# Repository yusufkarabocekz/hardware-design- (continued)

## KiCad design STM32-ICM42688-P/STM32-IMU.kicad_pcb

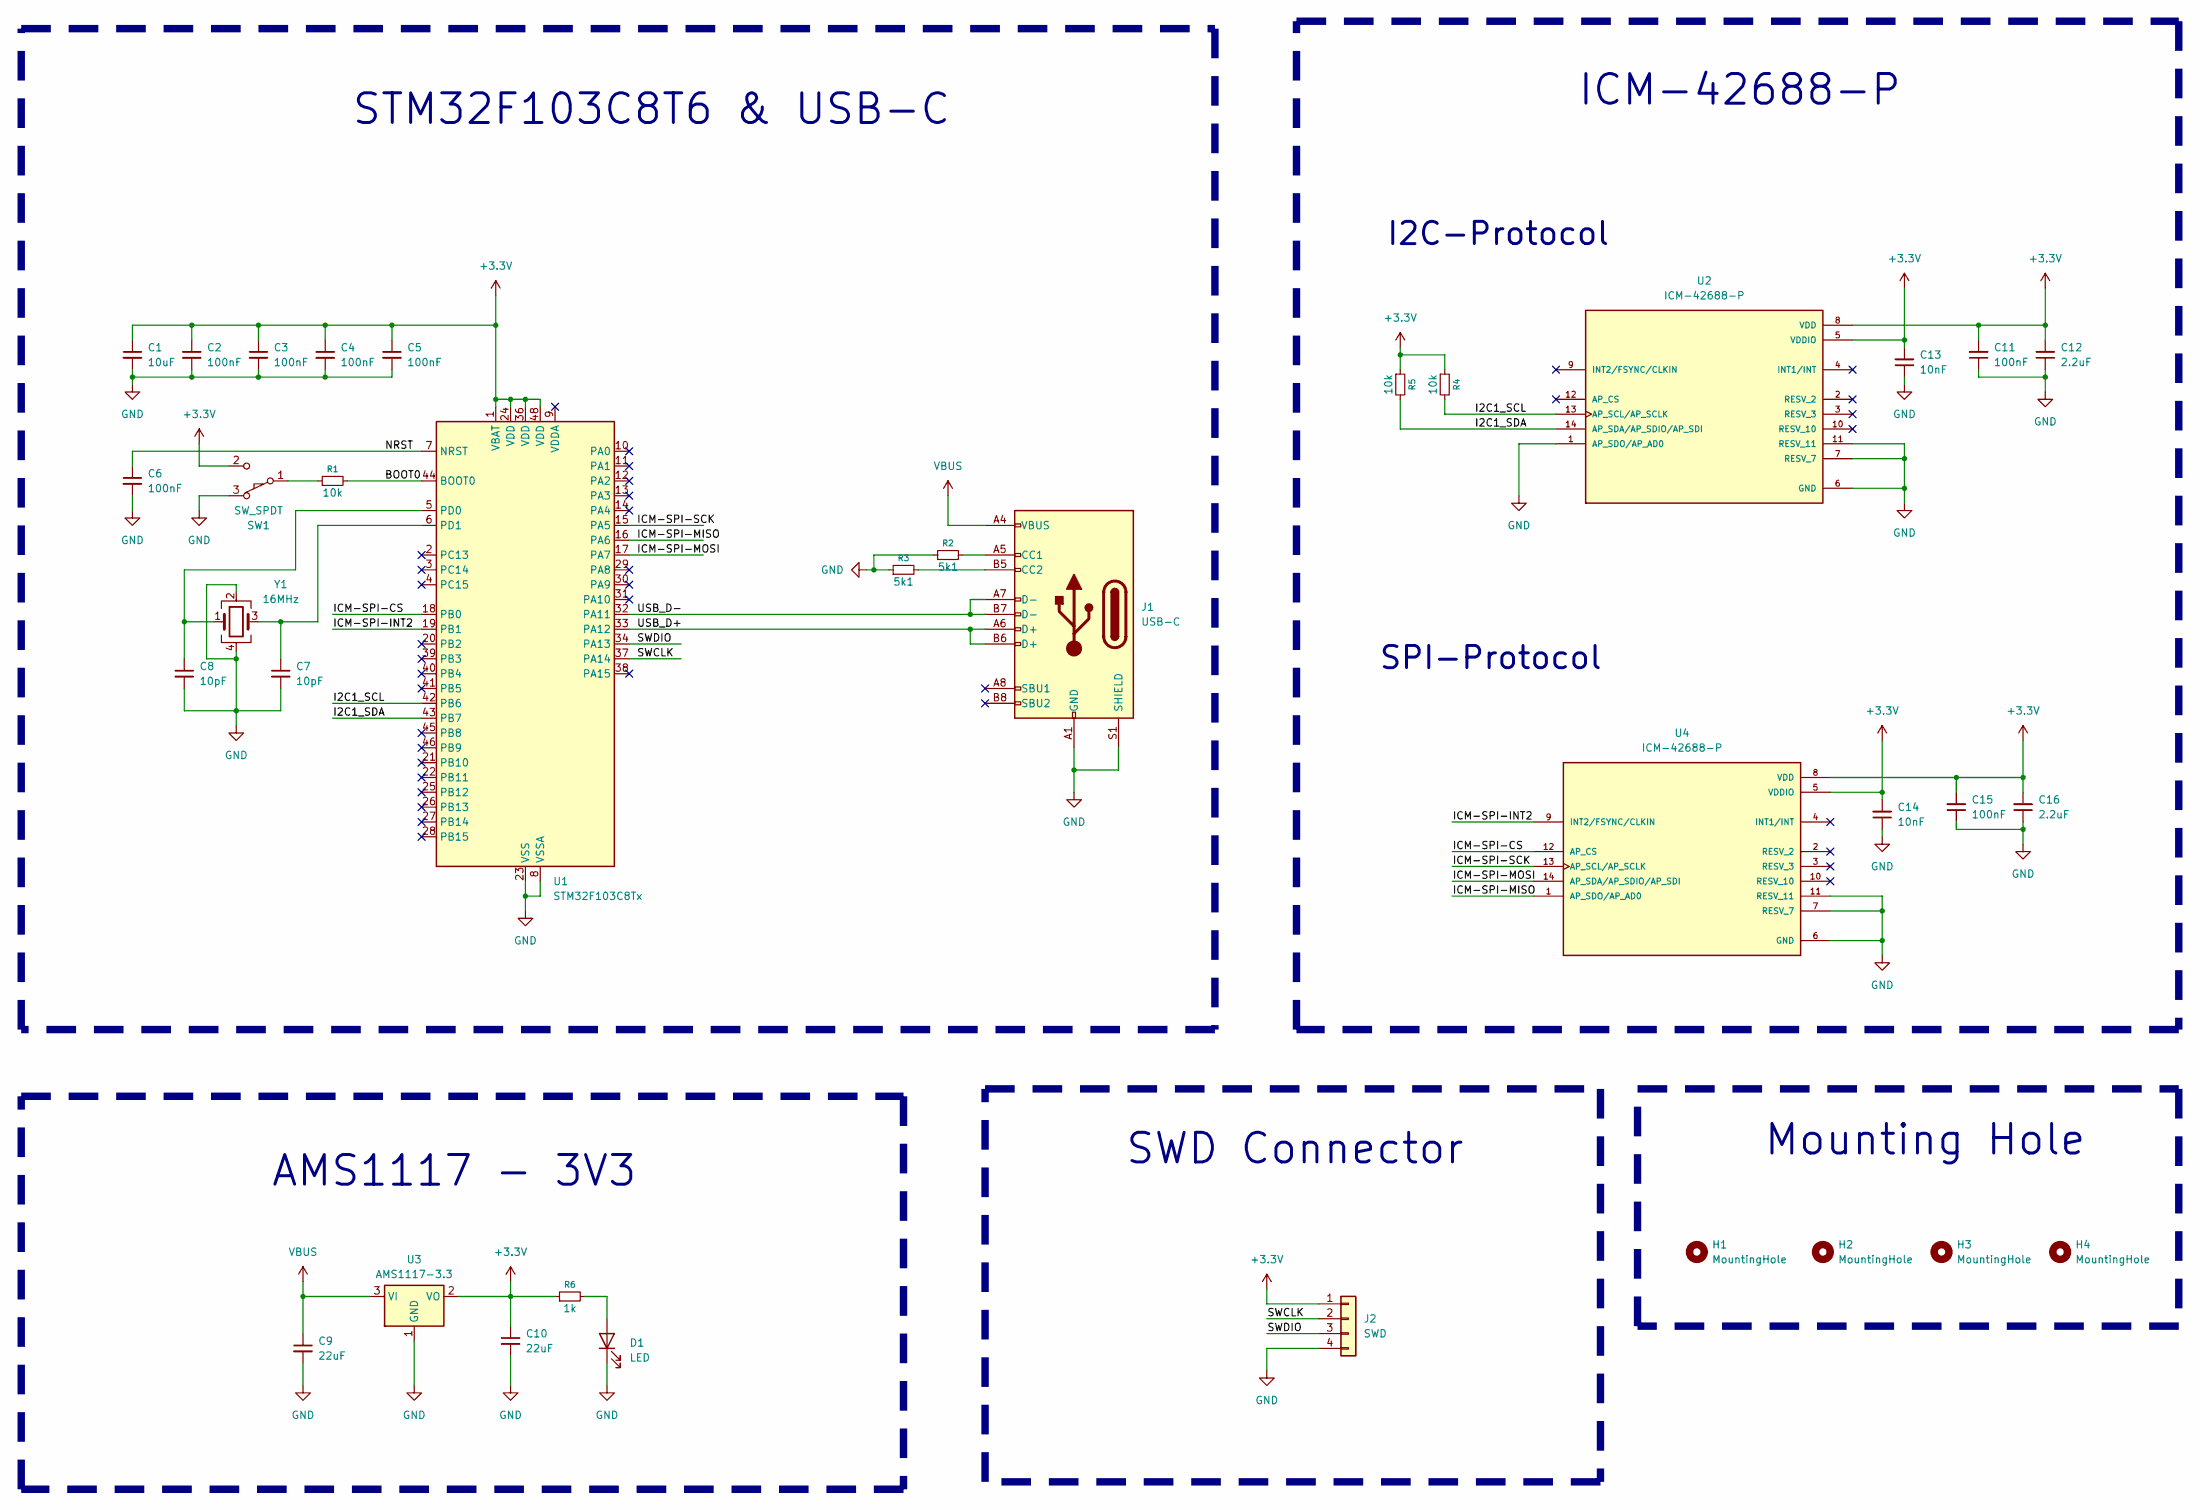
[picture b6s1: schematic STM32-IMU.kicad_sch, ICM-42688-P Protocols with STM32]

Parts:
C1: 10uF; C_0603_1608Metric
C2, C3, C4, C5, C6, C11, C15: 100nF; C_0603_1608Metric
C7, C8: 10pF; C_0603_1608Metric
C9, C10: 22uF; C_0805_2012Metric
C12, C16: 2.2uF; C_0603_1608Metric
C13, C14: 10nF; C_0603_1608Metric
D1: LED; LED_0805_2012Metric
H1, H2, H3, H4: MountingHole; MountingHole_3.2mm_M3_ISO7380
J1: USB-C; USB_C_Receptacle_GCT_USB4105-xx-A_16P_TopMnt_Horizontal
J2: SWD; PinHeader_1x04_P2.54mm_Vertical
R1, R4, R5: 10k; R_0603_1608Metric
R2, R3: 5k1; R_0603_1608Metric
R6: 1k; R_0603_1608Metric
SW1: SW_SPDT; SW_SPDT_PCM12
U1: STM32F103C8Tx; LQFP-48_7x7mm_P0.5mm
U2, U4: ICM-42688-P; PQFN50P300X250X97-14N; PARTREV 1.2
U3: AMS1117-3.3; SOT-223-3_TabPin2
Y1: 16MHz; Crystal_SMD_3225-4Pin_3.2x2.5mm

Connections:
+3.3V: C1.1, C2.1, C3.1, C4.1, C5.1, C10.1, C11.2, C12.2, C13.2, C14.2, C15.2, C16.2, J2.1, R4.1, R5.1, R6.1, SW1.2 (B), U1.1 (VBAT), U1.24 (VDD), U1.36 (VDD), U1.48 (VDD), U2.5 (VDDIO), U2.8 (VDD), U3.2 (VO), U4.5 (VDDIO), U4.8 (VDD)
/BOOT0: R1.2, U1.44 (BOOT0)
/I2C1_SCL: R4.2, U1.42 (PB6), U2.13 (AP_SCL/AP_SCLK)
/I2C1_SDA: R5.2, U1.43 (PB7), U2.14 (AP_SDA/AP_SDIO/AP_SDI)
/ICM-SPI-CS: U1.18 (PB0), U4.12 (AP_CS)
/ICM-SPI-INT2: U1.19 (PB1), U4.9 (INT2/FSYNC/CLKIN)
/ICM-SPI-MISO: U1.16 (PA6), U4.1 (AP_SDO/AP_AD0)
/ICM-SPI-MOSI: U1.17 (PA7), U4.14 (AP_SDA/AP_SDIO/AP_SDI)
/ICM-SPI-SCK: U1.15 (PA5), U4.13 (AP_SCL/AP_SCLK)
/NRST: C6.1, U1.7 (NRST)
/SWCLK: J2.2, U1.37 (PA14)
/SWDIO: J2.3, U1.34 (PA13)
/USB_D+: J1.A6 (D+), J1.B6 (D+), U1.33 (PA12)
/USB_D-: J1.A7 (D-), J1.B7 (D-), U1.32 (PA11)
GND: C1.2, C2.2, C3.2, C4.2, C5.2, C6.2, C7.2, C8.2, C9.2, C10.2, C11.1, C12.1, C13.1, C14.1, C15.1, C16.1, D1.1 (K), J1.A1 (GND), J1.A12 (GND), J1.B1 (GND), J1.B12 (GND), J1.S1 (SHIELD), J2.4, R2.1, R3.1, SW1.3 (C), U1.8 (VSSA), U1.23 (VSS), U1.35 (VSS), U1.47 (VSS), U2.1 (AP_SDO/AP_AD0), U2.6 (GND), U2.7 (RESV_7), U2.11 (RESV_11), U3.1 (GND), U4.6 (GND), U4.7 (RESV_7), U4.11 (RESV_11), Y1.2, Y1.4
unnamed: D1.2 (A), R6.2
unnamed: J1.A5 (CC1), R2.2
unnamed: J1.B5 (CC2), R3.2
unnamed: R1.1, SW1.1 (A)
unnamed: C8.1, U1.5 (PD0), Y1.1
unnamed: C7.1, U1.6 (PD1), Y1.3
VBUS: C9.1, J1.A4 (VBUS), J1.A9 (VBUS), J1.B4 (VBUS), J1.B9 (VBUS), U3.3 (VI)

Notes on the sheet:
I2C-Protocol
SPI-Protocol
SWD Connector
STM32F103C8T6 & USB-C
Mounting Hole
AMS1117 - 3V3
ICM-42688-P

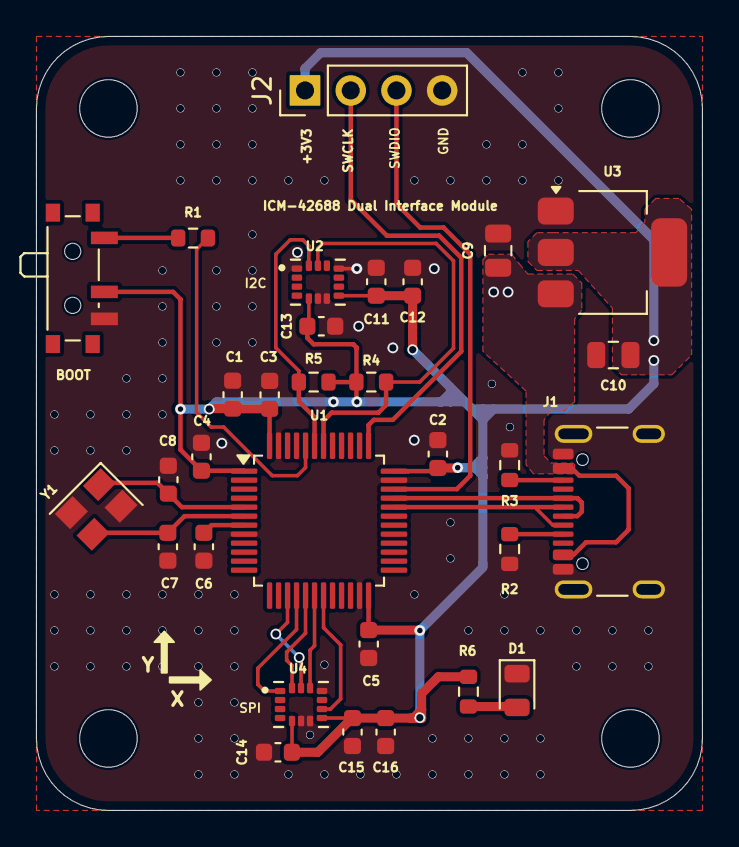
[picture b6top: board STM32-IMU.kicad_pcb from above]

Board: 2 copper layers, 37.0 x 43.0 mm, 35 parts (0 on the bottom side), 22 nets.

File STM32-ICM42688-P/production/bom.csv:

Designator,Footprint,Quantity,Value,LCSC Part #
C1,0603,1,10uF,
"C10, C9",0805,2,22uF,
"C11, C15, C2, C3, C4, C5, C6",0603,7,100nF,
"C12, C16",0603,2,2.2uF,
"C13, C14",0603,2,10nF,
"C7, C8",0603,2,10pF,
D1,0805,1,LED,
J1,USB_C_Receptacle_GCT_USB4105-xx-A_16P_TopMnt_Horizontal,1,USB-C,
J2,PinHeader_1x04_P2.54mm_Vertical,1,SWD,
R1,0603,1,10k,
"R2, R3",0603,2,5k1,
"R4, R5",0603,2,4k7,
R6,0603,1,1k,
SW1,SW_SPDT_PCM12,1,SW_SPDT,
U1,LQFP-48_7x7mm_P0.5mm,1,STM32F103C8Tx,
"U2, U4",PQFN50P300X250X97-14N,2,ICM-42688-P,
U3,SOT-223-3_TabPin2,1,AMS1117-3.3,
Y1,Crystal_SMD_3225-4Pin_3.2x2.5mm,1,16MHz,

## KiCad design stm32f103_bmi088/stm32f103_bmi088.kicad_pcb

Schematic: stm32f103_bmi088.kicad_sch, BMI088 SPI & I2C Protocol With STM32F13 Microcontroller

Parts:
C1, C2: 1uF; C_0805_2012Metric
C3, C4, C5, C6, C8, C10, C11, C13, C14: 100nF; C_0402_1005Metric
C7: 10uF; C_0603_1608Metric
C9, C12: 20pF; C_0402_1005Metric
D1: LED; LED_0805_2012Metric
H1, H2, H3, H4: GND; MountingHole_3.2mm_M3_Pad_Via
J1: USB_B_Micro; USB_Micro-B_Molex_47346-0001
J2: SWD; PinSocket_1x04_P2.54mm_Horizontal
R1, R2: 4.7k; R_0402_1005Metric
R3: 1k; R_0402_1005Metric
R4, R5: 220; R_0402_1005Metric
R6: 1M; R_0402_1005Metric
R7: 10k; R_0402_1005Metric
SW1: BOOT; SW_SPDT_PCM12
U1: MIC5504-3.3YM5; SOT-23-5
U2, U3: BMI088; PQFN50P450X300X100-16N
U4: STM32F103C8Tx; LQFP-48_7x7mm_P0.5mm
Y1: 16MHz; Crystal_HC49-4H_Vertical

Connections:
+3V3: C2.1, C3.1, C4.1, C5.1, C6.1, C7.1, C10.1, C11.1, C13.1, C14.1, J2.1, R1.2, R2.2, R3.1, SW1.2 (B), U1.5 (VOUT), U2.3 (VDD), U2.7 (PS), U2.11 (VDDIO), U2.14 (CSB1), U3.3 (VDD), U3.11 (VDDIO), U4.1 (VBAT), U4.24 (VDD), U4.36 (VDD), U4.48 (VDD); also elsewhere on the board
/A0_ACCEL: U2.15 (SDO1), U4.38 (PA15)
/A0_GYRO: U2.10 (SDO2), U4.41 (PB5)
/BMI088_MISO: U3.10 (SDO2), U3.15 (SDO1), U4.16 (PA6)
/BMI088_MOSI: U3.9 (SDA/SDI), U4.17 (PA7)
/BMI088_SCK: U3.8 (SCL/SCK), U4.15 (PA5)
/BMI088_SCL: R2.1, U2.8 (SCL/SCK), U4.42 (PB6)
/BMI088_SDA: R1.1, U2.9 (SDA/SDI), U4.43 (PB7)
/CSB_ACCEL: U3.14 (CSB1), U4.20 (PB2)
/CSB_GYRO: U3.5 (CSB2), U4.14 (PA4)
/INT1_ACCEL: U3.16 (INT1), U4.21 (PB10)
/INT1_ACCEL_I: U2.16 (INT1), U4.39 (PB3)
/INT2_ACCEL: U3.1 (INT2), U4.22 (PB11)
/INT2_ACCEL_I: U2.1 (INT2), U4.40 (PB4)
/INT3_GYRO: U3.12 (INT3), U4.18 (PB0)
/INT3_GYRO_I: U2.12 (INT3), U4.45 (PB8)
/INT4_GYRO: U3.13 (INT4), U4.19 (PB1)
/INT4_GYRO_I: U2.13 (INT4), U4.46 (PB9)
/SWCLK: J2.2, U4.37 (PA14)
/SWDIO: J2.3, U4.34 (PA13)
/USB_D+: R4.1, U4.33 (PA12)
/USB_D-: R5.2, U4.32 (PA11)
GND: C1.2, C2.2, C3.2, C4.2, C5.2, C6.2, C7.2, C8.2, C9.2, C10.2, C11.2, C12.2, C13.2, C14.2, D1.1 (K), H1.1, H2.1, H3.1, H4.1, J1.5 (GND), J2.4, SW1.3 (C), U1.2 (GND), U2.2 (NC), U2.4 (GNDA), U2.6 (GNDIO), U3.2 (NC), U3.4 (GNDA), U3.6 (GNDIO), U3.7 (PS), U4.8 (VSSA), U4.23 (VSS), U4.35 (VSS), U4.47 (VSS); also elsewhere on the board
unnamed: D1.2 (A), R3.2
unnamed: J1.3 (D+), R4.2
unnamed: J1.2 (D-), R5.1
unnamed 26: R7.1, SW1.1 (A); also elsewhere on the board
unnamed: R7.2, U4.44 (BOOT0)
unnamed: C8.1, U4.7 (NRST)
unnamed: C9.1, R6.1, U4.5 (PD0), Y1.2
unnamed: C12.1, R6.2, U4.6 (PD1), Y1.1
VBUS: C1.1, J1.1 (VBUS), U1.1 (VIN)

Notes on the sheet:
STM32F103 Microcontroller
BMI088 SPI Protocol
BMI088 I2C Protocol
Regulator && USB && SWD

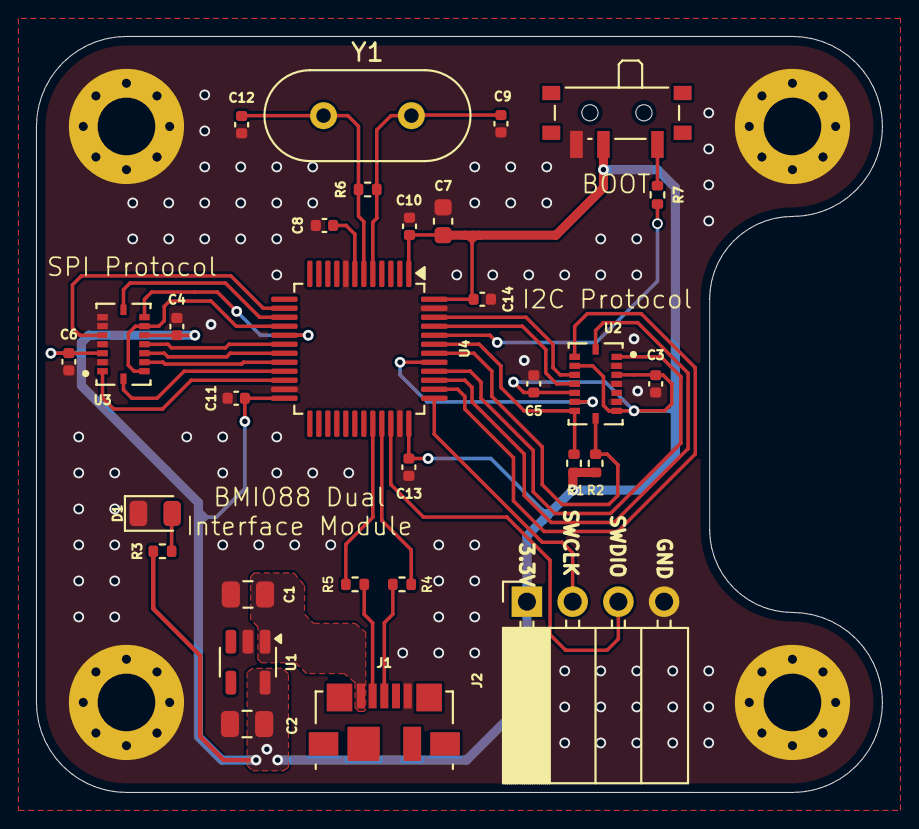
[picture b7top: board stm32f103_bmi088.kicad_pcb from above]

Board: 2 copper layers, 47.0 x 42.0 mm, 34 parts (0 on the bottom side), 32 nets.

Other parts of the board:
BOOT: BOOT; SW_SPDT_PCM12

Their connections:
+3V3: BOOT.2 (B); also elsewhere on the board
GND: BOOT.3 (C); also elsewhere on the board
unnamed 26: BOOT.1 (A); also elsewhere on the board

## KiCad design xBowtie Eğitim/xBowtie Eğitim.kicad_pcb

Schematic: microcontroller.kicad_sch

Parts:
BZ1: Buzzer; MagneticBuzzer_ProSignal_ABT-410-RC
C11, C16, C17, C21: 1uF; C_0805_2012Metric
C12: 470uF; CP_Elec_10x10.5
C13, C14, C15, C18, C23, C24, C25, C26, C27: 100nF; C_0603_1608Metric
C19, C22: 4.7uF; C_0805_2012Metric
C29, C30: 20pF; C_0603_1608Metric
D5: 1N4148; D_SMA
Q4, Q5: MMBT3904; SOT-23
R10, R14, R15, R18, R19, R20, R21, R22, R39, R40, R41, R42: 100R; R_0603_1608Metric
R11: 1K; R_0603_1608Metric
R16, R17: 4.7k; R_0603_1608Metric
R23, R24: 15R; R_0603_1608Metric
SW1: SW_Wuerth_450301014042; SW_SPDT_PCM12
U3: M41T62Q; SO-8_3.9x4.9mm_P1.27mm
U4: Texas_HSOP-8-1EP_3.9x4.9mm_P1.27mm
U5: ESP32-WROOM-32
U6: STM32F103C6Tx; LQFP-48_7x7mm_P0.5mm
Y1: 32.768kHz; Crystal_SMD_MicroCrystal_CM9V-T1A-2Pin_1.6x1.0mm
Y2: 16MHz; Crystal_SMD_SeikoEpson_TSX3225-4Pin_3.2x2.5mm

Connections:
3V3DC: C11.1, C14.1, C15.1, C16.1, C17.1, C18.1, C19.1, C21.1, C22.1, C23.1, C24.1, C25.1, C26.1, D5.2 (A), R11.1, R16.2, R17.2, R42.1, U3.8 (VCC), U4.8 (VCC), U5.2 (VDD), U6.9 (VDDA), U6.24 (VDD), U6.36 (VDD), U6.48 (VDD); also elsewhere on the board
5VDC: BZ1.1 (+), C13.1; also elsewhere on the board
/Microcontroller/BUZZER: R21.1, R39.2
/Microcontroller/NRST: C27.1, R14.1, U6.7 (NRST)
/Microcontroller/RTC_SCL: R16.1, U3.6 (SCL), U6.42 (PB6)
/Microcontroller/RTC_SDA: R17.1, U3.5 (SDA), U6.43 (PB7)
/Microcontroller/SENSOR_ON/OFF: R41.2, U6.20 (PB2)
/Microcontroller/TEMP_IN_CS: R18.1, U6.14 (PA4)
/Microcontroller/TEMP_IN_OT: R40.1, U6.46 (PB9)
/Microcontroller/TEMP_IN_SCLK: R19.1, U6.15 (PA5)
/Microcontroller/TEMP_IN_SIO: R20.1, U6.17 (PA7)
/Microcontroller/WIFI_EN: R10.1, R22.1
/Microcontroller/WIFI_OUT: Q5.3 (C), R11.2, U5.3 (EN)
/Microcontroller/WIFI_RXD: U5.6 (IO34), U6.12 (PA2)
/Microcontroller/WIFI_TXD: U5.7 (IO35), U6.13 (PA3)
GND: C11.2, C12.2, C13.2, C14.2, C15.2, C16.2, C17.2, C18.2, C19.2, C21.2, C22.2, C23.2, C24.2, C25.2, C26.2, C27.2, C29.1, C30.1, Q4.2 (E), Q5.2 (E), R14.2, R15.1, U3.4 (VSS), U4.4 (GND), U5.1 (GND), U5.15 (GND), U5.38 (GND), U5.39 (GND), U6.8 (VSSA), U6.23 (VSS), U6.35 (VSS), U6.47 (VSS), Y2.2, Y2.4; also elsewhere on the board
LED_DRIVER: U6.21 (PB10); also elsewhere on the board
MCU_RLY_1: U6.41 (PB5); also elsewhere on the board
MCU_RLY_2: U6.40 (PB4); also elsewhere on the board
unnamed: BZ1.2 (-), Q4.3 (C)
unnamed: C12.1, D5.1 (K), U3.3 (VBAT)
unnamed: Q4.1 (B), R39.1
unnamed: Q5.1 (B), R10.2
unnamed: R41.1, SW1.1 (B)
unnamed: R42.2, SW1.2 (C)
unnamed: U3.1 (OSC_IN), Y1.2
unnamed: U3.2 (OSC_OUT), Y1.1
unnamed: R18.2, U4.2 (CS)
unnamed: R40.2, U4.5 (OT)
unnamed: R19.2, U4.1 (SCLK)
unnamed: R20.2, U4.3 (SIO)
unnamed: R15.2, U6.44 (BOOT0)
unnamed: R23.1, U6.32 (PA11)
unnamed: R24.1, U6.33 (PA12)
unnamed: R22.2, U6.18 (PB0)
unnamed: R21.2, U6.27 (PB14)
unnamed: C30.2, U6.3 (PC14), Y2.3
unnamed: C29.2, U6.4 (PC15), Y2.1
PIR_DETECTOR: U6.22 (PB11); also elsewhere on the board
SWCLK: U6.37 (PA14); also elsewhere on the board
SWDIO: U6.34 (PA13); also elsewhere on the board
TDI: U6.38 (PA15); also elsewhere on the board
TEMPERATURE_ADC: U6.19 (PB1); also elsewhere on the board
USB_N: R23.2; also elsewhere on the board
USB_P: R24.2; also elsewhere on the board

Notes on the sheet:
STM32F103C6T6
SENSOR ON/OFF
ESP32
BUZZER
TEMPERATURE SENSOR
RTC

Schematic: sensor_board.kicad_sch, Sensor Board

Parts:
C28, C37, C38, C39, C43: 100nF; C_0603_1608Metric
C31, C40, C44: 4.7uF; C_0805_2012Metric
C32, C41, C42: 1uF; C_0805_2012Metric
C33, C35: 10nF; C_0603_1608Metric
C34, C36: 33uF; C_1206_3216Metric
D7, D8: LED; LED_0805_2012Metric
J8: Conn_01x06; JST_GH_SM06B-GHS-TB_1x06-1MP_P1.25mm_Horizontal
Q3: MMBT3904; SOT-23
R25, R31, R35: 10k; R_0603_1608Metric
R26, R28, R33: 1k; R_0603_1608Metric
R27: 100k; R_0603_1608Metric
R29: 100R; R_0603_1608Metric
R30, R32: 560k; R_0603_1608Metric
R34: 220k; R_0603_1608Metric
R36: 43k; R_0603_1608Metric
R37, R38: 0R; R_0603_1608Metric
S1: TO5
TH1: Thermistor_PTC; R_1206_3216Metric
U8: OPA310xDBV; SOT-23-5
U9: NCS36000; SO14

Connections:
3V3DC_S: C28.1, C40.1, C41.2, C42.2, C43.1, C44.1, J8.1, R29.2, R33.1, R34.1, TH1.1, U8.5 (V+), U9.14 (VDD)
/Sensor Board/LED_S: J8.3, R28.2
/Sensor Board/TEMP_ADC: C32.2, J8.4, R27.1
GND_S: C28.2, C31.2, C32.1, C37.2, C38.1, C39.2, C40.2, C41.1, C42.1, C43.2, C44.2, J8.2, Q3.2 (E), R25.1, R35.2, R36.1, R37.2, R38.2, S1.3 (GND), U8.2 (V-), U9.7 (VSS)
unnamed: C31.1, R26.1, R27.2
unnamed: C34.2, R31.2
unnamed: C36.1, R35.1
unnamed: D7.2 (A), R29.1
unnamed: D7.1 (K), Q3.3 (C)
unnamed: D8.2 (A), R33.2
unnamed: D8.1 (K), U9.9 (LED)
unnamed: Q3.1 (B), R28.1
unnamed: C38.2, S1.1 (D), U9.6 (VREF)
unnamed: C37.1, R36.2, S1.2 (S), U9.5 (OP1_P)
unnamed: R25.2, TH1.2, U8.3 (+)
unnamed: R26.2, U8.1, U8.4 (-)
unnamed: R38.1, U9.12 (MODE)
unnamed: C35.2, C36.2, R32.1, U9.4 (OP1_N)
unnamed: C34.1, C35.1, R32.2, U9.3 (OP1_O)
unnamed: C33.1, R30.2, R31.1, U9.2 (OP2_N)
unnamed: C33.2, R30.1, U9.1 (OP2_O)
unnamed: C39.1, R34.2, U9.13 (OSC)
unnamed: R37.1, U9.10 (~LED_EN)
PIR_DETECT: J8.5, U9.8 (OUT)

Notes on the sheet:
CONNECTOR
TEMPERATURE SENSOR AND FILTER
LED_DRIVER
PIR DETECTOR

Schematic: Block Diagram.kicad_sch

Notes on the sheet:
I/O
ADC
PWM
220V AC to 12V DC
USB/UART
I2C
SPI
UART
12V DC to 5V - 3.3V DC
RTC
DC-DC CONVERTER
Sistem 220V AC 50Hz Türkiye ev şebeke bağlantısı ile çalışabilmelidir. Sistemden kullanıcıya kullanabileceği 12V DC ve 5V DC güç çıkışları olmalıdır. Sistem USB arayüzü ile bilgisayara bağlanabilir ve veri aktarabilir olmalıdır. Sistem gerçek zamanlı saat bilgisini kullanıcıya verebilmelidir. Siste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
KOMPONENTLER: RTC: M41T006MF WIFI MODULE: ESP32-WROOM-32E (4 MB) PYRO SENSOR: LHI878 TEMPERATURE OUTSIDE: TFPT1206 TEMPERATURE INSIDE: MAX6662 MCU: STM32F103C6T6 RELAY: ALQ112 BUZZER: CMI-9650IC - 0580T SENSOR ON/OFF: EG1215AA AC-DC CONVERTER: BV302S12010-ZU Bridge Rectifier: DB105STR DC-DC CONVERT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
RELAY
PROGRAMMING CONNECTOR
USB
12V & 5V DC OUTPUT
TEMPERATURE SENSOR
MCU
PYROELECTRIC SENSOR (PIR)
Wi-Fi MODULE
SENSOR ON/OFF
LED DRIVER CIRCUIT
BUZZER
AC-DC CONVERTER

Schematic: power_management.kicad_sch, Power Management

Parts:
C1, C2: 470uF; CP_Elec_10x10.5
C3, C7, C10, C47: 1uF; C_0805_2012Metric
C4: 68uF; CP_Elec_6.3x5.8
C5, C8: 100nF; C_0603_1608Metric
C6: 10nF; C_0603_1608Metric
C9, C20, C45, C46: 4.7uF; C_0805_2012Metric
D1: MDB10S; DIP-4_W7.62mm
D2: B350A-13-F; D_SMA
D3, D4, D6, D9: 1N4148; D_SMA
F1: Polyfuse; Fuse_1206_3216Metric
J1: AC_LINE; PhoenixContact_MSTBA_2,5_2-G_1x02_P5.00mm_Horizontal
J2: LIGHT_1; PhoenixContact_MSTBA_2,5_2-G_1x02_P5.00mm_Horizontal
J3: LIGHT_2; PhoenixContact_MSTBA_2,5_2-G_1x02_P5.00mm_Horizontal
J4: USER_IO; PinSocket_1x05_P2.54mm_Horizontal
J5: 12VDC; BarrelJack_Horizontal
J6: 5VDC; BarrelJack_Horizontal
J7: USB_C_Receptacle_USB2.0_16P; USB_C_Receptacle_GCT_USB4105-xx-A_16P_TopMnt_Horizontal
J9: Conn_01x06; JST_GH_SM06B-GHS-TB_1x06-1MP_P1.25mm_Horizontal
K1, K2: ALQ112; RELAY_ALQ112
L1: 47uH; L_Chilisin_BMRB00060650
Q1, Q2: BC547; TO-92_Inline
R1: 270m; R_Axial_Power_L20.0mm_W6.4mm_P22.40mm
R2, R4: 1k; R_0603_1608Metric
R3, R5: 10k; R_0603_1608Metric
R12, R13: 5.1k; R_0603_1608Metric
T1: BV302S12010-ZU; Transformer_Breve_TEZ-22x24
U1: LM2675M-5; SOIC-8_3.9x4.9mm_P1.27mm
U2: AP7361C-10E; SOT-223-3_TabPin2
U7: USBLC6-2SC6; SOT-23-6

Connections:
3V3DC: C9.1, C10.1, C45.1, C46.1, C47.2, J4.1, J9.1, U2.3 (VO), U7.5 (VBUS); also elsewhere on the board
5VDC: C4.1, C7.1, C8.1, C20.2, D6.1 (K), J6.1, L1.2, U1.4 (FB), U2.1 (VI); also elsewhere on the board
12VDC: C3.1, C5.1, D3.1 (K), D4.1 (K), D9.1 (K), J5.1, K1.1, K2.1, U1.7 (VIN)
/Power Management/LIGHT_1_GND: J2.2, K1.4
/Power Management/LIGHT_1_VCC: J2.1, K1.5
/Power Management/LIGHT_2_GND: J3.2, K2.4
/Power Management/LIGHT_2_VCC: J3.1, K2.5
AC_LINE_1: J1.1, R1.1
AC_LINE_2: J1.2, T1.4 (AB)
D+: J7.A6 (D+), J7.B6 (D+), U7.6 (I/O1)
D-: J7.A7 (D-), J7.B7 (D-), U7.4 (I/O2)
GND: C1.2, C2.2, C3.2, C4.2, C5.2, C7.2, C8.2, C9.2, C10.2, C20.1, C45.2, C46.2, C47.1, D1.4, D2.2 (A), J4.5, J5.2, J5.3, J6.2, J6.3, J7.A1 (GND), J7.A12 (GND), J7.B1 (GND), J7.B12 (GND), J9.2, Q1.3 (E), Q2.3 (E), R3.1, R5.1, R12.1, R13.1, U1.6 (GND), U2.2 (GND), U7.2 (GND); also elsewhere on the board
LED_DRIVER: J9.3; also elsewhere on the board
MCU_RLY_1: R2.1; also elsewhere on the board
MCU_RLY_2: R4.1; also elsewhere on the board
unnamed: D1.1 (+), T1.8 (SB)
unnamed: D1.2 (-), T1.5 (SA)
unnamed: D1.3, F1.1
unnamed: C6.2, D2.1 (K), L1.1, U1.8 (VSW)
unnamed: D3.2 (A), K1.2, Q1.1 (C)
unnamed: D4.2 (A), K2.2, Q2.1 (C)
unnamed: D6.2 (A), J7.A4 (VBUS), J7.A9 (VBUS), J7.B4 (VBUS), J7.B9 (VBUS)
unnamed: C1.1, C2.1, D9.2 (A), F1.2
unnamed: J7.A5 (CC1), R12.2
unnamed: J7.B5 (CC2), R13.2
unnamed: Q1.2 (B), R2.2, R3.2
unnamed: Q2.2 (B), R4.2, R5.2
unnamed: R1.2, T1.1 (AA)
unnamed: C6.1, U1.1 (CB)
PIR_DETECTOR: J9.5; also elsewhere on the board
SWCLK: J4.3; also elsewhere on the board
SWDIO: J4.2; also elsewhere on the board
TDI: J4.4; also elsewhere on the board
TEMPERATURE_ADC: J9.4; also elsewhere on the board
USB_N: U7.3 (I/O2); also elsewhere on the board
USB_P: U7.1 (I/O1); also elsewhere on the board

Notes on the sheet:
[5VDC- 3VDC] DC-DC CONVERTER
[12VDC- 5VDC] DC-DC CONVERTER
AC/DC CONVERTER
RELAY
CONNECTOR

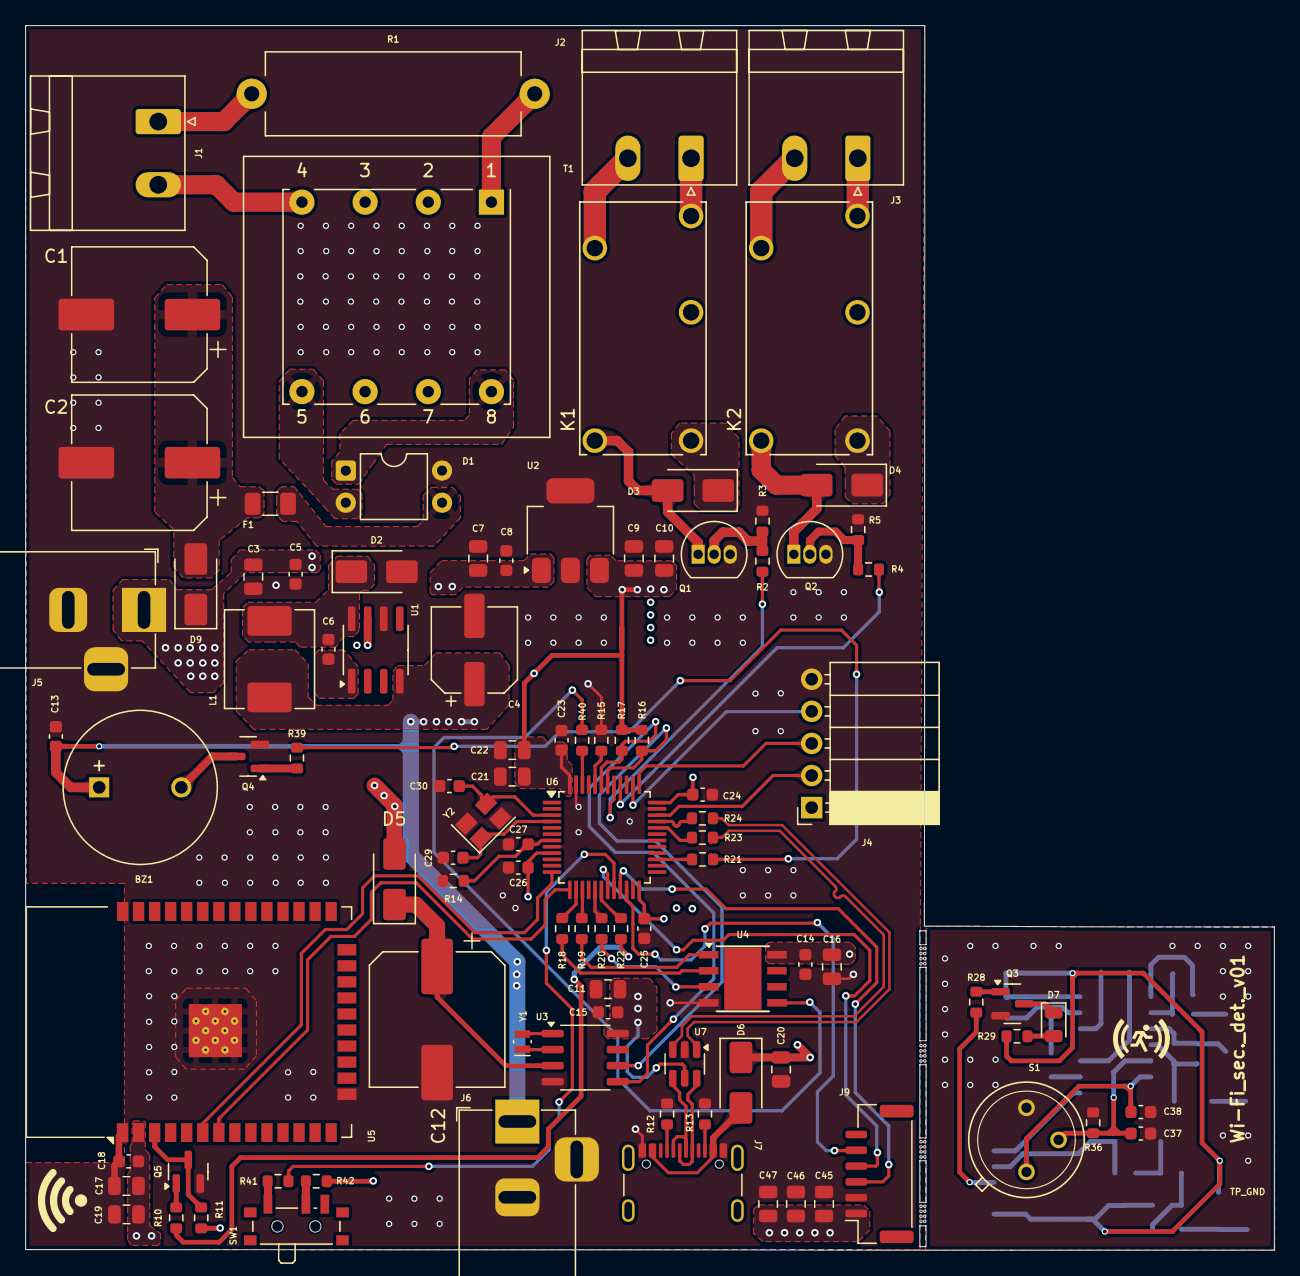
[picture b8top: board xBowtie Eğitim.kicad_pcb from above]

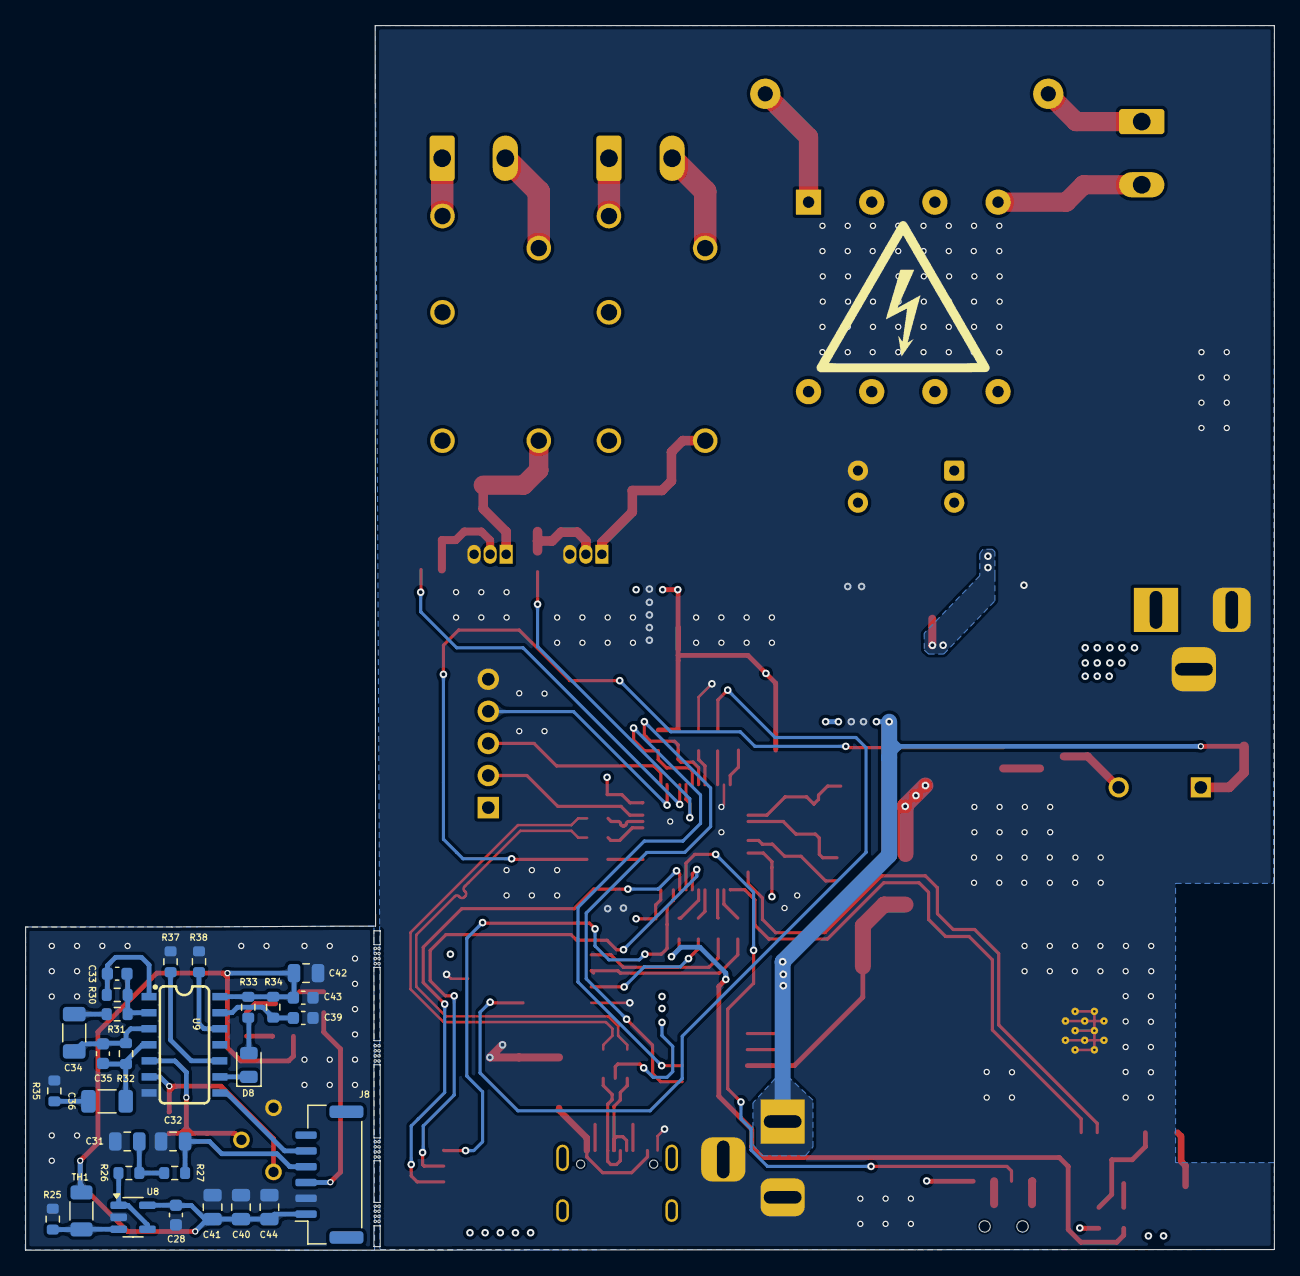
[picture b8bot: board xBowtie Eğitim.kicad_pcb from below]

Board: 4 copper layers, 98.8 x 96.9 mm, 128 parts (29 on the bottom side), 92 nets.

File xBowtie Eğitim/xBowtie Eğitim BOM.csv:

"Id";"Designator";"Footprint";"Quantity";"Designation";"Supplier and ref";
1;"C12,C1,C2";"CP_Elec_10x14.3";3;"470uF";;;
2;"J1";"PhoenixContact_MSTBA_2,5_2-G_1x02_P5.00mm_Horizontal";1;"AC_LINE";;;
3;"C27,C38,C37,C14,C24,C26,C13,C18,C23,C5,C15,C8,C25,C43,C39,C28";"C_0603_1608Metric";16;"100nF";;;
4;"R4,R2,R28,R33,R26";"R_0603_1608Metric";5;"1k";;;
5;"C4";"CP_Elec_6.3x5.8";1;"68uF";;;
6;"R15,R20,R19,R29,R10,R18,R40,R22,R42,R41,R14,R21,R39";"R_0603_1608Metric";13;"100R";;;
7;"C22,C46,C20,C19,C9,C45,C40,C31,C44";"C_0805_2012Metric";9;"4.7uF";;;
8;"R16,R17";"R_0603_1608Metric";2;"4.7k";;;
9;"J9,J8";"JST_GH_SM06B-GHS-TB_1x06-1MP_P1.25mm_Horizontal";2;"Conn_01x06";;;
10;"C3,C10,C47,C21,C17,C16,C11,C7,C32,C41,C42";"C_0805_2012Metric";11;"1uF";;;
11;"F1";"Fuse_1206_3216Metric";1;"Polyfuse";;;
12;"R3,R5,R35,R31,R25";"R_0603_1608Metric";5;"10k";;;
13;"U3";"SO-8_3.9x4.9mm_P1.27mm";1;"M41T62Q";;;
14;"D3,D4,D6,D9,D5";"D_SMA";5;"1N4148";;;
15;"C29,C30";"C_0603_1608Metric";2;"20pF";;;
16;"R36";"R_0603_1608Metric";1;"43k";;;
17;"U2";"SOT-223-3_TabPin2";1;"AP7361C-10E";;;
18;"U4";"Texas_HSOP-8-1EP_3.9x4.9mm_P1.27mm";1;"~";;;
19;"R1";"R_Axial_Power_L20.0mm_W6.4mm_P22.40mm";1;"270m";;;
20;"D7,D8";"LED_0805_2012Metric";2;"LED";;;
21;"Q4,Q5,Q3";"SOT-23";3;"MMBT3904";;;
22;"J4";"PinSocket_1x05_P2.54mm_Horizontal";1;"USER_IO";;;
23;"SW1";"SW_SPDT_PCM12";1;"SW_Wuerth_450301014042";;;
24;"K2,K1";"RELAY_ALQ112";2;"ALQ112";;;
25;"R12,R13";"R_0603_1608Metric";2;"5.1k";;;
26;"D2";"D_SMA";1;"B350A-13-F";;;
27;"Y1";"Crystal_SMD_MicroCrystal_CM9V-T1A-2Pin_1.6x1.0mm";1;"32.768kHz";;;
28;"U6";"LQFP-48_7x7mm_P0.5mm";1;"STM32F103C6Tx";;;
29;"U1";"SOIC-8_3.9x4.9mm_P1.27mm";1;"LM2675M-5";;;
30;"R23,R24";"R_0603_1608Metric";2;"15R";;;
31;"L1";"L_Chilisin_BMRB00060650";1;"47uH";;;
32;"U7";"SOT-23-6";1;"USBLC6-2SC6";;;
33;"U5";"ESP32-WROOM-32";1;"ESP32-WROOM-32";;;
34;"D1";"DIP-4_W7.62mm";1;"MDB10S";;;
35;"Q1,Q2";"TO-92_Inline";2;"BC547";;;
36;"T1";"Transformer_Breve_TEZ-22x24";1;"BV302S12010-ZU";;;
37;"C6,C33,C35";"C_0603_1608Metric";3;"10nF";;;
38;"R11";"R_0603_1608Metric";1;"1K";;;
39;"J2";"PhoenixContact_MSTBA_2,5_2-G_1x02_P5.00mm_Horizontal";1;"LIGHT_1";;;
40;"S1";"TO5";1;"~";;;
41;"J7";"USB_C_Receptacle_GCT_USB4105-xx-A_16P_TopMnt_Horizontal";1;"USB_C_Receptacle_USB2.0_16P";;;
42;"J3";"PhoenixContact_MSTBA_2,5_2-G_1x02_P5.00mm_Horizontal";1;"LIGHT_2";;;
43;"J6";"BarrelJack_Horizontal";1;"5VDC";;;
44;"J5";"BarrelJack_Horizontal";1;"12VDC";;;
45;"Y2";"Crystal_SMD_SeikoEpson_TSX3225-4Pin_3.2x2.5mm";1;"16MHz";;;
46;"BZ1";"MagneticBuzzer_ProSignal_ABT-410-RC";1;"Buzzer";;;
47;"R34";"R_0603_1608Metric";1;"220k";;;
48;"C36,C34";"C_1206_3216Metric";2;"33uF";;;
49;"TH1";"R_1206_3216Metric";1;"Thermistor_PTC";;;
50;"R37,R38";"R_0603_1608Metric";2;"0R";;;
51;"R27";"R_0603_1608Metric";1;"100k";;;
52;"R32,R30";"R_0603_1608Metric";2;"560k";;;
53;"U8";"SOT-23-5";1;"OPA310xDBV";;;
54;"U9";"SO14";1;"NCS36000";;;

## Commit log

2025-06-04 add LM2596 Buck Converter && XL6009 Boost Converter
2025-06-04 add xBowtie education project
2025-06-10 add stm32f103 & bmi088 project
2025-06-10 add STM32-ICM42688-P IMU project
2025-06-11 add industrial sensor module && UKB
2025-06-13 add autopilot && power distrubiton projects
2025-06-13 remove backups files
2025-07-23 remove html file
2025-07-23 remove .g4 file
